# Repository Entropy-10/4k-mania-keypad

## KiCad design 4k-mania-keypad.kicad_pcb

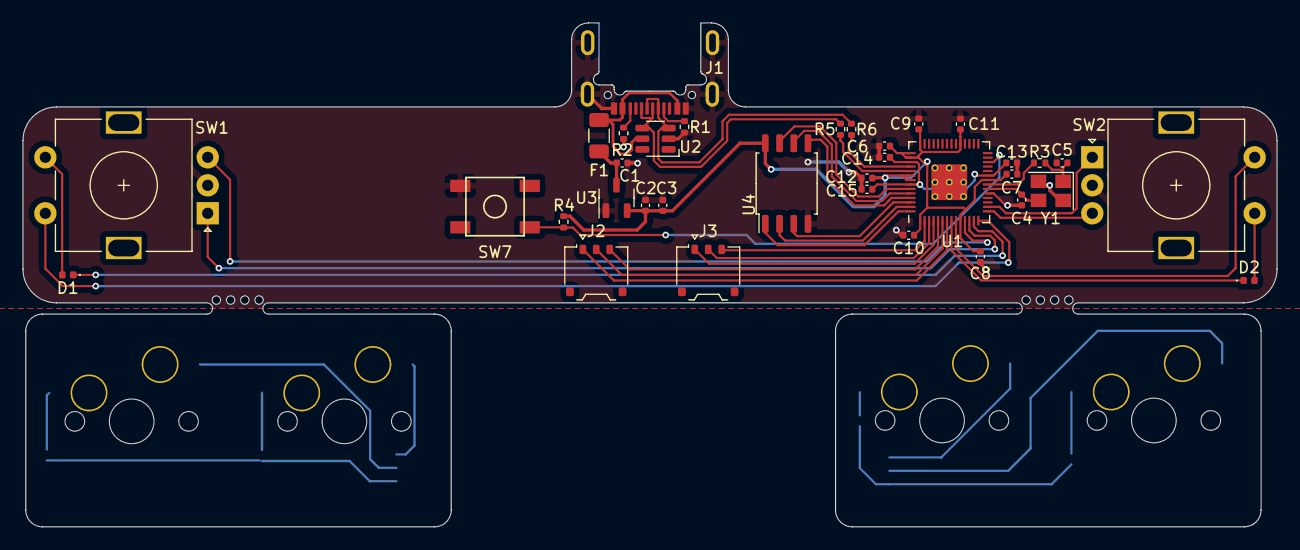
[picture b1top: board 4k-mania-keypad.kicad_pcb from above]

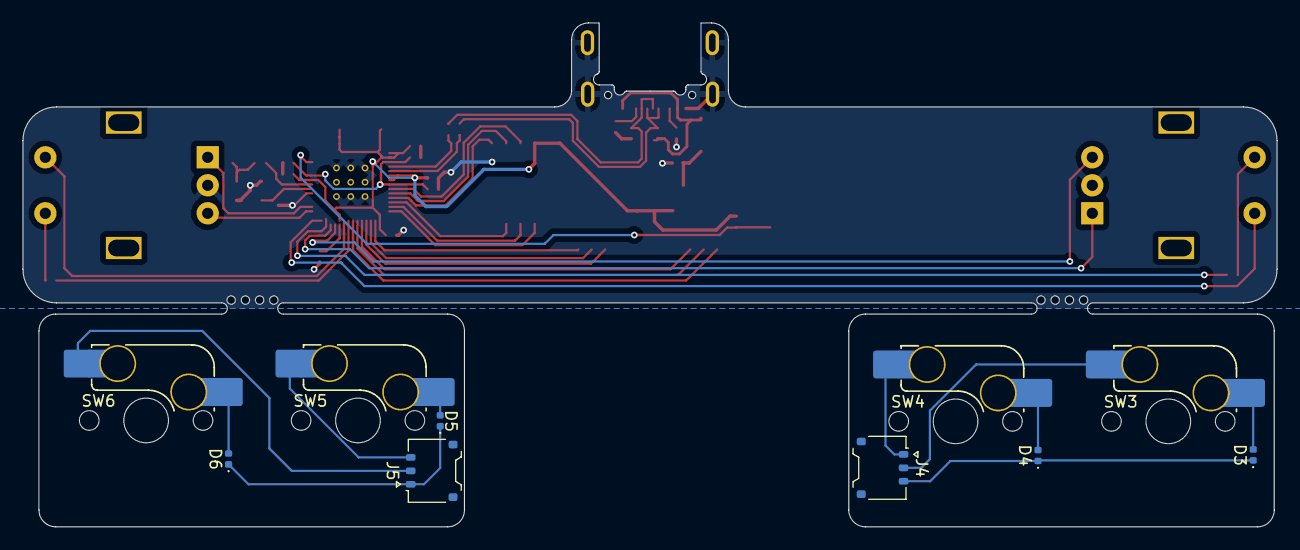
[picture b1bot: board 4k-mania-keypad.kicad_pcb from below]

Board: 2 copper layers, 112.0 x 45.0 mm, 45 parts (10 on the bottom side), 47 nets.

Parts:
C1, C2, C12, C15: 1uF; C_0402_1005Metric
C3, C6, C7, C8, C9, C10, C11, C13, C14: 100nF; C_0402_1005Metric
C4, C5: 27pF; C_0402_1005Metric
D1, D2, D3, D4, D5, D6: d; D_0402_1005Metric
F1: 500mA; Fuse_1206_3216Metric
J1: USB_C_Receptacle_USB2.0; USB_C_Receptacle_HRO_TYPE-C-31-M-14
J2, J3, J4, J5: Pico Ezmate; Molex_Pico-EZmate_78171-0003_1x03-1MP_P1.20mm_Vertical
R1, R2: 5.1k; R_0402_1005Metric
R3, R4: 1k; R_0402_1005Metric
R5, R6: 27.4; R_0402_1005Metric
SW1, SW2: EC11E18244A5; RotaryEncoder_Alps_EC11E-Switch_Vertical_H20mm
SW3, SW4, SW5, SW6: MX_SW_HS; SW_MX_HS_1u
SW7: SW_Push; SKQG-1155865
U1: RP2040; RP2040-QFN-56
U2: SRV05-4; SOT-23-6-routable
U3: XC6206; SOT-23-3
U4: W25Q128JVS; SOIC-8_5.23x5.23mm_P1.27mm
Y1: 12MHz; Crystal_SMD_3225-4Pin_3.2x2.5mm

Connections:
+1V1: C13.1, C14.1, C15.1, U1.23 (DVDD), U1.45 (VREG_VOUT), U1.50 (DVDD)
+3.3V: C2.1, C3.1, C6.1, C7.1, C8.1, C9.1, C10.1, C11.1, C12.1, R4.1, U1.1 (IOVDD), U1.10 (IOVDD), U1.22 (IOVDD), U1.33 (IOVDD), U1.42 (IOVDD), U1.43 (ADC_AVDD), U1.44 (VREG_VIN), U1.48 (USB_VDD), U1.49 (IOVDD), U3.2 (VO), U4.8 (VCC)
+5V: C1.1, F1.2, U3.3 (VI)
/CLK: U1.52 (QSPI_SCLK), U4.6 (CLK)
/CS: U1.56 (QSPI_SS_N), U4.1 (~CS)
/SD0: U1.53 (QSPI_SD0), U4.5 (DI(IO0))
/SD1: U1.55 (QSPI_SD1), U4.2 (DO(IO1))
/SD2: U1.54 (QSPI_SD2), U4.3 (IO2)
/SD3: U1.51 (QSPI_SD3), U4.7 (IO3)
/USB_D+: J1.A6 (D+), J1.B6 (D+), R5.1, U2.4 (IO3)
/USB_D-: J1.A7 (D-), J1.B7 (D-), R6.1, U2.3 (IO2)
/col0(0): J2.1, U1.7 (GPIO5)
/col0(1): J3.3, U1.2 (GPIO0)
/col1(0): J2.2, U1.6 (GPIO4)
/col1(1): J3.2, U1.3 (GPIO1)
/reset: R4.2, SW7.1, U1.26 (~RUN)
/rotA(0): SW1.A, U1.12 (GPIO9)
/rotA(1): SW2.A, U1.16 (GPIO13)
/rotB(0): SW1.B, U1.11 (GPIO8)
/rotB(1): SW2.B, U1.15 (GPIO12)
/row0(0): J2.3, U1.5 (GPIO3)
/row0(1): J3.1, U1.4 (GPIO2)
/rsw0(0): SW1.S2, U1.14 (GPIO11)
/rsw0(1): SW2.S2, U1.9 (GPIO7)
/rsw1(0): D1.1 (K), U1.13 (GPIO10)
/rsw1(1): D2.1 (K), U1.8 (GPIO6)
GND: C1.2, C2.2, C3.2, C4.1, C5.1, C6.2, C7.2, C8.2, C9.2, C10.2, C11.2, C12.2, C13.2, C14.2, C15.2, J1.A1 (GND), J1.A12 (GND), J1.B1 (GND), J1.B12 (GND), J1.S1 (SHIELD), R1.1, R2.2, SW1.C, SW2.C, SW7.2, U1.19 (TESTEN), U1.57 (GND), U2.2 (VN), U3.1 (GND), U4.4 (GND), Y1.2, Y1.4
unnamed: C5.2, R3.1, Y1.1
unnamed: D1.2 (A), SW1.S1
unnamed: D2.2 (A), SW2.S1
unnamed: D3.2 (A), SW3.1
unnamed: D3.1 (K), D4.1 (K), J4.3
unnamed: D4.2 (A), SW4.1
unnamed: D5.2 (A), SW5.1
unnamed: D5.1 (K), D6.1 (K), J5.1
unnamed: D6.2 (A), SW6.1
unnamed: J1.A5 (CC1), R1.2
unnamed: J1.B5 (CC2), R2.1
unnamed: J4.1, SW4.2
unnamed: J4.2, SW3.2
unnamed: J5.2, SW6.2
unnamed: J5.3, SW5.2
unnamed: R5.2, U1.47 (D+)
unnamed: R6.2, U1.46 (D-)
unnamed: C4.2, U1.20 (XTAL_IN), Y1.3
unnamed: R3.2, U1.21 (XTAL_OUT)
VCC: F1.1, J1.A4 (VBUS), J1.A9 (VBUS), J1.B4 (VBUS), J1.B9 (VBUS), U2.5 (VP)

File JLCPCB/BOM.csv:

"Source:","C:\Users\jaele\Desktop\4k-mania-keypad\4k-mania-keypad.kicad_sch"
"Date:","2/23/2023 7:28:08 PM"
"Tool:","Eeschema (7.0.0)"
"Generator:","C:\Program Files\KiCad\7.0\bin\scripting\plugins/bom_csv_grouped_by_value_with_fp.py"
"Component Count:","45"
"Ref","Qnty","Value","Cmp name","Footprint","Description","Vendor","DNP"
"C1, C2, C12, C15","4","1uF","C_Small","Capacitor_SMD:C_0402_1005Metric","Unpolarized capacitor, small symbol","C52923",""
"C3, C6, C7, C8, C9, C10, C11, C13, C14","9","100nF","C_Small","Capacitor_SMD:C_0402_1005Metric","Unpolarized capacitor, small symbol","C307331",""
"C4, C5","2","27pF","C_Small","Capacitor_SMD:C_0402_1005Metric","Unpolarized capacitor, small symbol","C1557",""
"D1, D2, D3, D4, D5, D6","6","d","D_Small","Diode_SMD:D_0402_1005Metric","Diode, small symbol","C191023",""
"F1","1","500mA","Polyfuse_Small","Fuse:Fuse_1206_3216Metric","Resettable fuse, polymeric positive temperature coefficient, small symbol","C355568",""
"J1","1","USB_C_Receptacle_USB2.0","USB_C_Receptacle_USB2.0","marbastlib-various:USB_C_Receptacle_HRO_TYPE-C-31-M-14","USB 2.0-only Type-C Receptacle connector","C223907",""
"J2, J3, J4, J5","4","Pico Ezmate","Conn_01x03","Connector_Molex:Molex_Pico-EZmate_78171-0003_1x03-1MP_P1.20mm_Vertical","Generic connector, single row, 01x03, script generated (kicad-library-utils/schlib/autogen/connector/)","",""
"R1, R2","2","5.1k","R_Small","Resistor_SMD:R_0402_1005Metric","Resistor, small symbol","C103086",""
"R3","1","1k","R_Small","Resistor_SMD:R_0402_1005Metric","Resistor, small symbol","C11702",""
"R4","1","1k","R_Small","Resistor_SMD:R_0805_2012Metric","Resistor, small symbol","C11702",""
"R5, R6","2","27.4","R_Small","Resistor_SMD:R_0402_1005Metric","Resistor, small symbol","C31439",""
"SW1, SW2","2","EC11E18244A5","RotaryEncoder_Switch","Rotary_Encoder:RotaryEncoder_Alps_EC11E-Switch_Vertical_H20mm","Rotary encoder, dual channel, incremental quadrate outputs, with switch","C255515",""
"SW3, SW4, SW5, SW6","4","MX_SW_HS","MX_SW_HS","marbastlib-mx:SW_MX_HS_1u","Push button switch, normally open, two pins, 45° tilted","",""
"SW7","1","SW_Push","SW_Push","random-keyboard-parts:SKQG-1155865","Push button switch, generic, two pins","C388858",""
"U1","1","RP2040","RP2040","Footprints:RP2040-QFN-56","","C2040",""
"U2","1","SRV05-4","SRV05-4","marbastlib-various:SOT-23-6-routable","ESD Protection Diodes with Low Clamping Voltage, SOT-23-6","C85364",""
"U3","1","XC6206","XC6206PxxxMR","Package_TO_SOT_SMD:SOT-23-3","Positive 60-250mA Low Dropout Regulator, Fixed Output, SOT-23","C5446",""
"U4","1","W25Q128JVS","W25Q128JVS","Package_SO:SOIC-8_5.23x5.23mm_P1.27mm","128Mb Serial Flash Memory, Standard/Dual/Quad SPI, SOIC-8","C97521",""
"Y1","1","12MHz","Crystal_GND24_Small","Crystal:Crystal_SMD_3225-4Pin_3.2x2.5mm","Four pin crystal, GND on pins 2 and 4, small symbol","C9002",""

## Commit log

2023-02-16 first draft
2023-02-16 usb routing fix
2023-02-18 new base
2023-02-18 added submodules
2023-02-18 finished schematic revamp
2023-02-19 main pcb routing finished
2023-02-21 First finished draft
2023-02-24 fixed many issues and generated fab files
2023-12-24 Updated for ordering
2023-12-25 Improved usb power section layout
2024-01-25 Added photos of the physical r1 build
